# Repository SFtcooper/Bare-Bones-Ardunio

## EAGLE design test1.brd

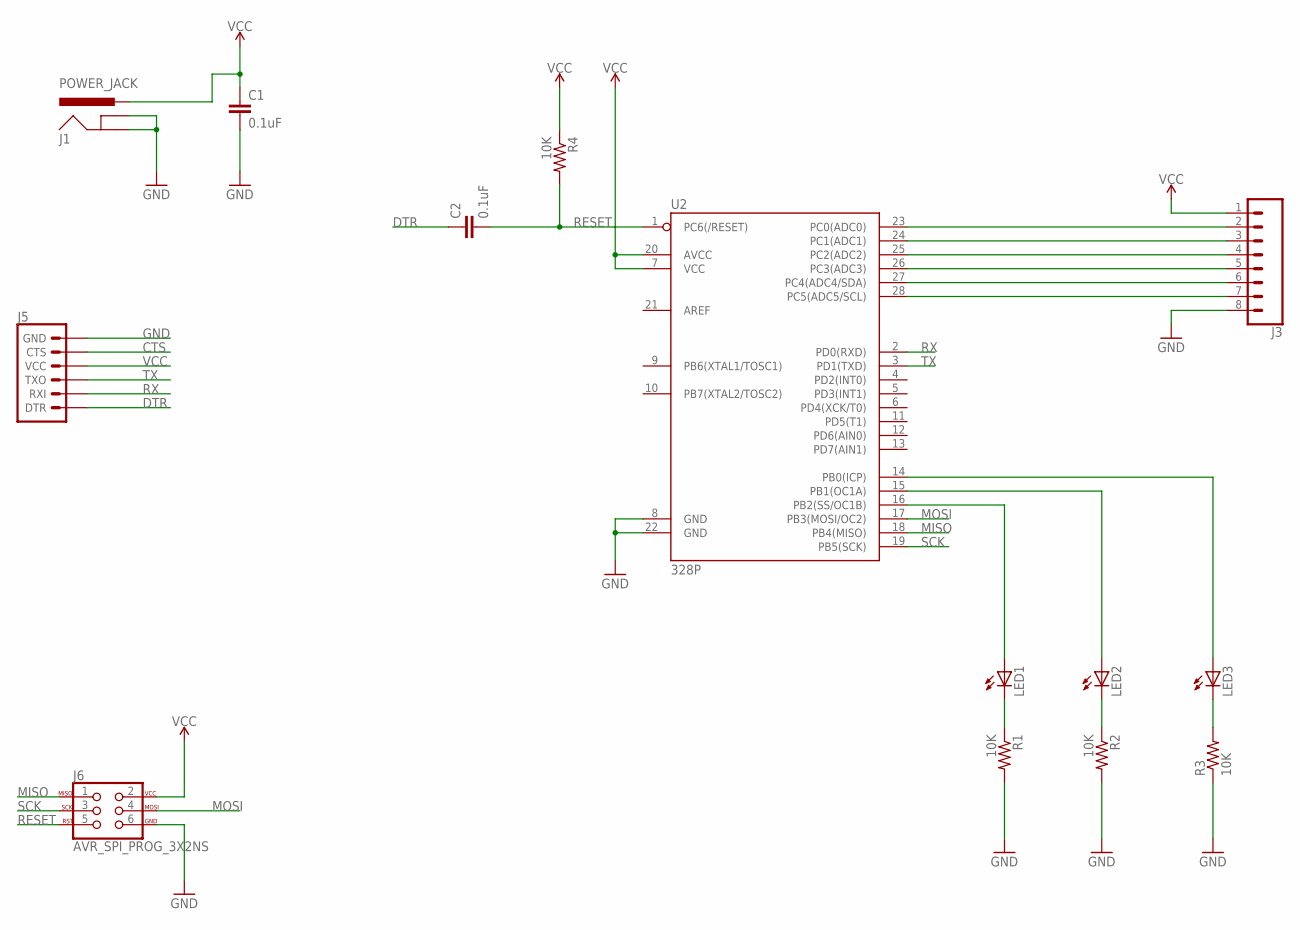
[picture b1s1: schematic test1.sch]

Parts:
C1, C2: 0.1uF; 0402-CAP
J1: POWER_JACK; POWER_JACK_PTH
J3: CONN_08"; 1X08
J5: 6_PIN_SERIAL_TARGET; 1X06
J6: AVR_SPI_PROG_3X2NS; 2X3-NS
LED1, LED2, LED3: LED5MM
R1, R2, R3, R4: 10K; M3216
U2: 328P; DIP28

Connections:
CTS: J5.5 (CTS)
DTR: C2.1, J5.1 (DTR)
GND: C1.2, J1.GND, J1.GNDBREAK, J3.8, J5.6 (GND), J6.6, R1.2, R2.2, R3.1, U2.8 (GND), U2.22 (GND)
MISO: J6.1, U2.18 (PB4(MISO))
MOSI: J6.4, U2.17 (PB3(MOSI/OC2))
unnamed: J3.2, U2.23 (PC0(ADC0))
unnamed: LED3.K (C), R3.2
unnamed: LED2.K (C), R2.1
unnamed: LED1.K (C), R1.1
unnamed: J3.3, U2.24 (PC1(ADC1))
unnamed: J3.4, U2.25 (PC2(ADC2))
unnamed: J3.5, U2.26 (PC3(ADC3))
unnamed: J3.6, U2.27 (PC4(ADC4/SDA))
unnamed: J3.7, U2.28 (PC5(ADC5/SCL))
unnamed: LED3.A, U2.14 (PB0(ICP))
unnamed: LED2.A, U2.15 (PB1(OC1A))
unnamed: LED1.A, U2.16 (PB2(SS/OC1B))
RESET: C2.2, J6.5, R4.2, U2.1 (PC6(/RESET))
RX: J5.2 (RXI), U2.2 (PD0(RXD))
SCK: J6.3, U2.19 (PB5(SCK))
TX: J5.3 (TXO), U2.3 (PD1(TXD))
VCC: C1.1, J1.PWR, J3.1, J5.4 (VCC), J6.2, R4.1, U2.7 (VCC), U2.20 (AVCC)

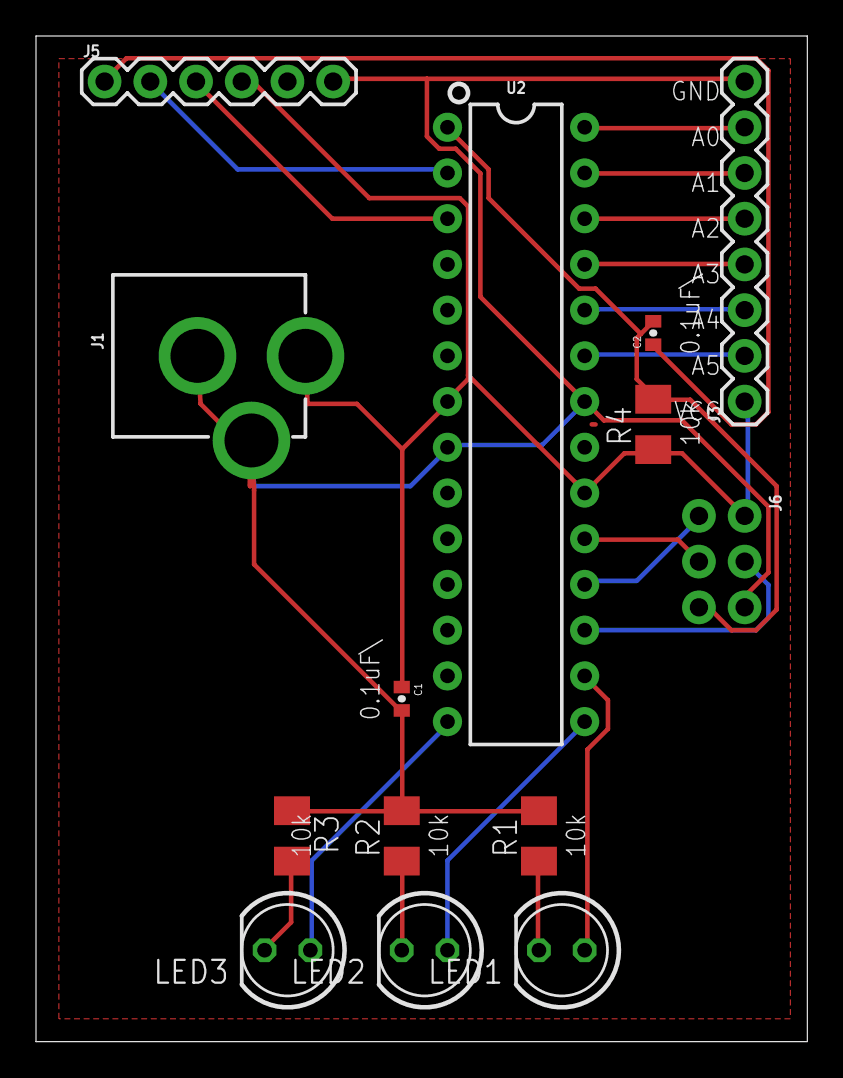
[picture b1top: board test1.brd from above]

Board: 2 copper layers, 42.9 x 55.9 mm, 14 parts (0 on the bottom side), 21 nets.

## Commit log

2017-04-23 :boom::camel: Added .gitattributes & .gitignore files
2017-04-23 Moving power input
    Slightly moving the power input connector for better fit
2017-04-23 s
    s

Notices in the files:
parts and their libraries:
SparkFun-Retired: Licensing: Creative Commons ShareAlike 4.0 International - https://creativecommons.org/licenses/by-sa/4.0
